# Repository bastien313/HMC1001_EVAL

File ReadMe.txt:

//******************************************************//
//**********	HMC1001 Evaluation board	********//
//**********	    By Bs Electronics           ********//
//**********            04/2019                 ********//
//******************************************************//

Board used to evaluate HMC1001 magnetic sensor.

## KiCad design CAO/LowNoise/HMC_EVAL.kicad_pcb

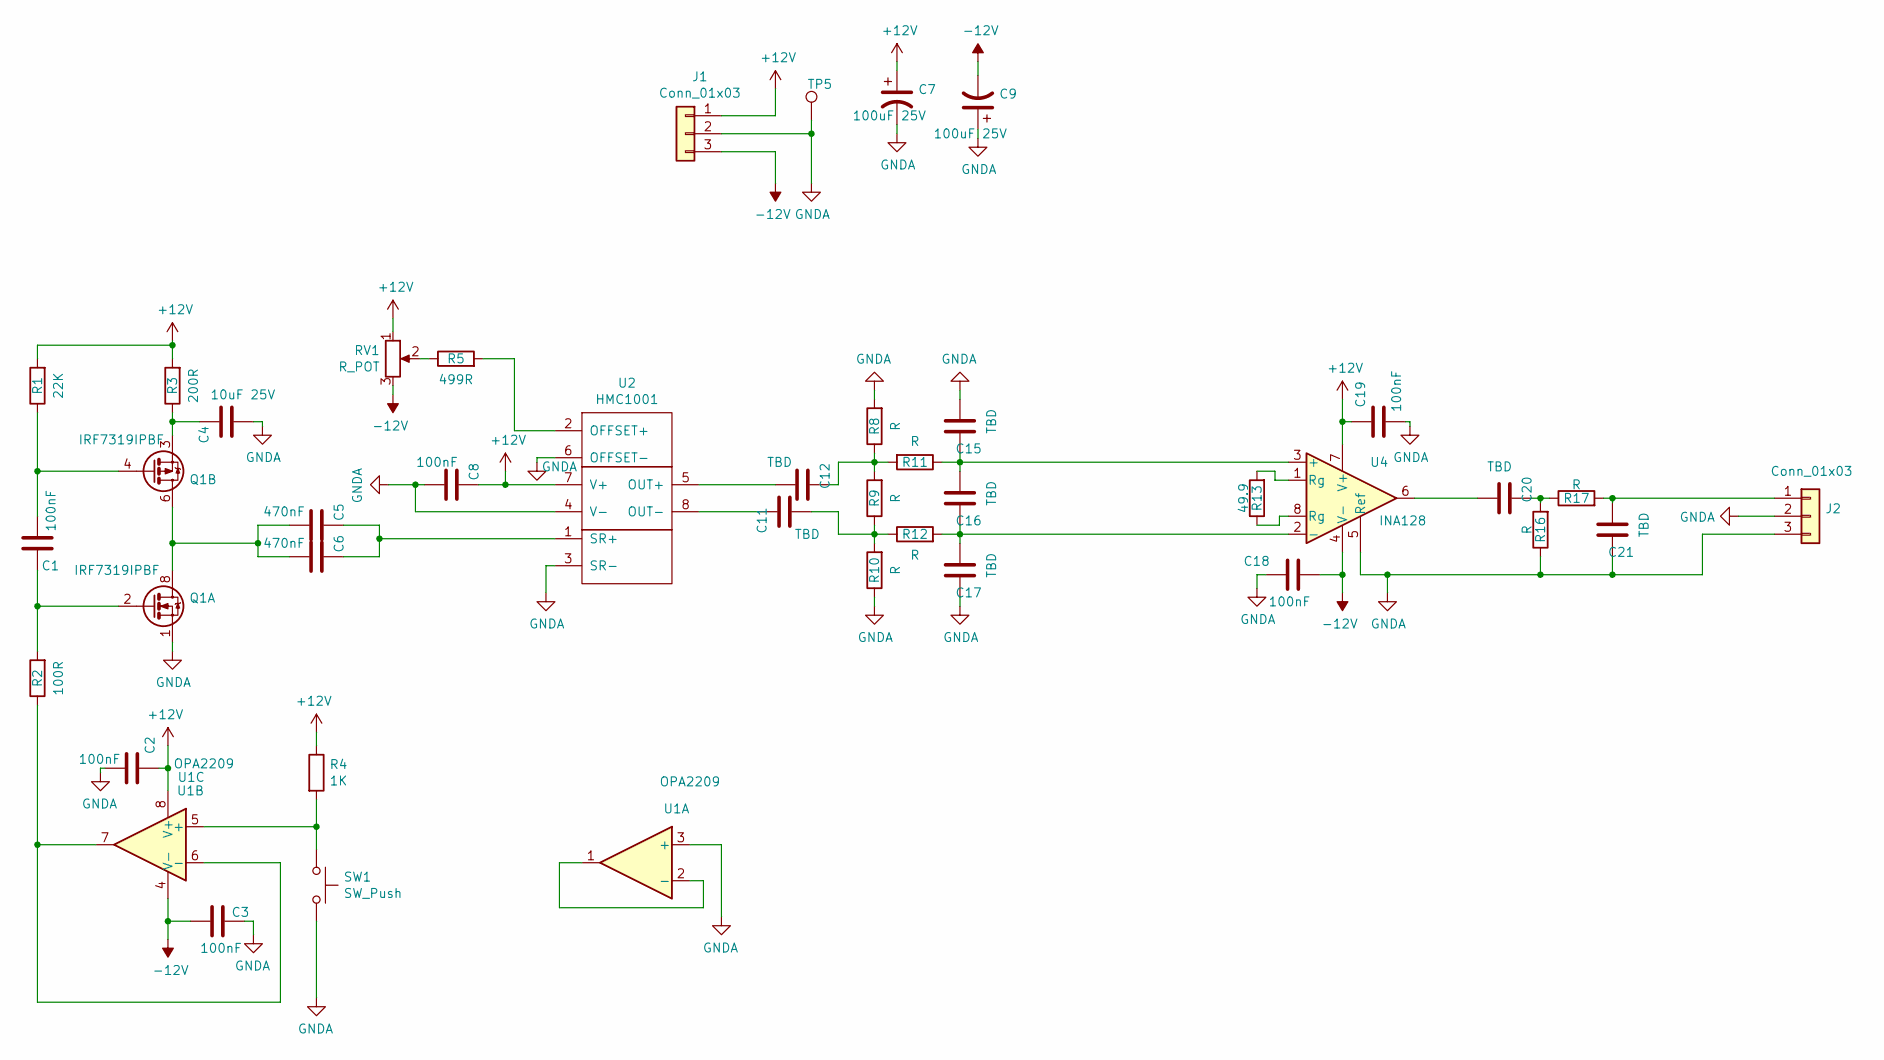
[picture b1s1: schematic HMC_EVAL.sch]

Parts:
C1, C2, C3, C8, C18, C19: 100nF; C_0805_HandSoldering
C4: 10uF 25V; C_1206_HandSoldering
C5, C6: 470nF; C_0805_HandSoldering
C7, C9: 100uF 25V; CP_Radial_D10.0mm_P5.00mm
C11, C12, C15, C16, C17, C20, C21: TBD; C_0805_HandSoldering
J1, J2: Conn_01x03; PhoenixContact_MSTBVA-G_03x5.08mm_Vertical
Q1: IRF7319IPBF; SOIC-8_3.9x4.9mm_Pitch1.27mm
R1: 22K; R_0805_HandSoldering
R2: 100R; R_1206_HandSoldering
R3: 200R; R_1206_HandSoldering
R4: 1K; R_0805_HandSoldering
R5: 499R; R_1206_HandSoldering
R8, R9, R10, R11, R12, R16, R17: R; R_0805_HandSoldering
R13: 49.9; R_0805_HandSoldering
RV1: R_POT; Potentiometer_Trimmer_Bourns_3296W
SW1: SW_Push; FSM2JSMA
TP5: TestPoint; SL-101-X-XX_1x01
U1: OPA2209; SOIC-8_3.9x4.9mm_Pitch1.27mm
U2: HMC1001; HCM1001
U4: INA128; SOIC-8_3.9x4.9mm_Pitch1.27mm

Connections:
+12V: C2.1, C7.1, C8.1, C19.1, J1.1, R1.2, R3.2, R4.1, RV1.1, U1.8 (V+), U2.7 (V+), U4.7 (V+)
-12V: C3.2, C9.2, C18.2, J1.3, RV1.3, U1.4 (V-), U4.4 (V-)
GNDA: C2.2, C3.1, C4.2, C7.2, C8.2, C9.1, C15.2, C17.1, C18.1, C19.2, C21.1, J1.2, J2.2, J2.3, Q1.1 (S), R8.2, R10.1, R16.1, SW1.2, TP5.1, U1.3 (+), U2.3 (SR-), U2.4 (V-), U2.6 (OFFSET-), U4.5 (Ref)
unnamed: C1.1, Q1.2 (G), R2.2
unnamed: C1.2, Q1.4 (G), R1.1
unnamed: C4.1, Q1.3 (1), R3.1
unnamed: C5.1, C6.1, U2.1 (SR+)
unnamed: C5.2, C6.2, Q1.5 (D), Q1.6 (D), Q1.7 (D), Q1.8 (D)
unnamed: C11.1, U2.8 (OUT-)
unnamed: C11.2, R9.1, R10.2, R12.1
unnamed: C12.1, R8.1, R9.2, R11.2
unnamed: C12.2, U2.5 (OUT+)
unnamed: C15.1, C16.2, R11.1, U4.3 (+)
unnamed: C16.1, C17.2, R12.2, U4.2 (-)
unnamed: C20.1, R16.2, R17.1
unnamed 15: C20.2, U4.6; also elsewhere on the board
unnamed: C21.2, J2.1, R17.2
unnamed: R2.1, U1.6 (-), U1.7
unnamed: R4.2, SW1.1, U1.5 (+)
unnamed: R5.1, RV1.2
unnamed: R5.2, U2.2 (OFFSET+)
unnamed: R13.1, U4.8 (Rg)
unnamed: R13.2, U4.1 (Rg)
unnamed: U1.1, U1.2 (-)

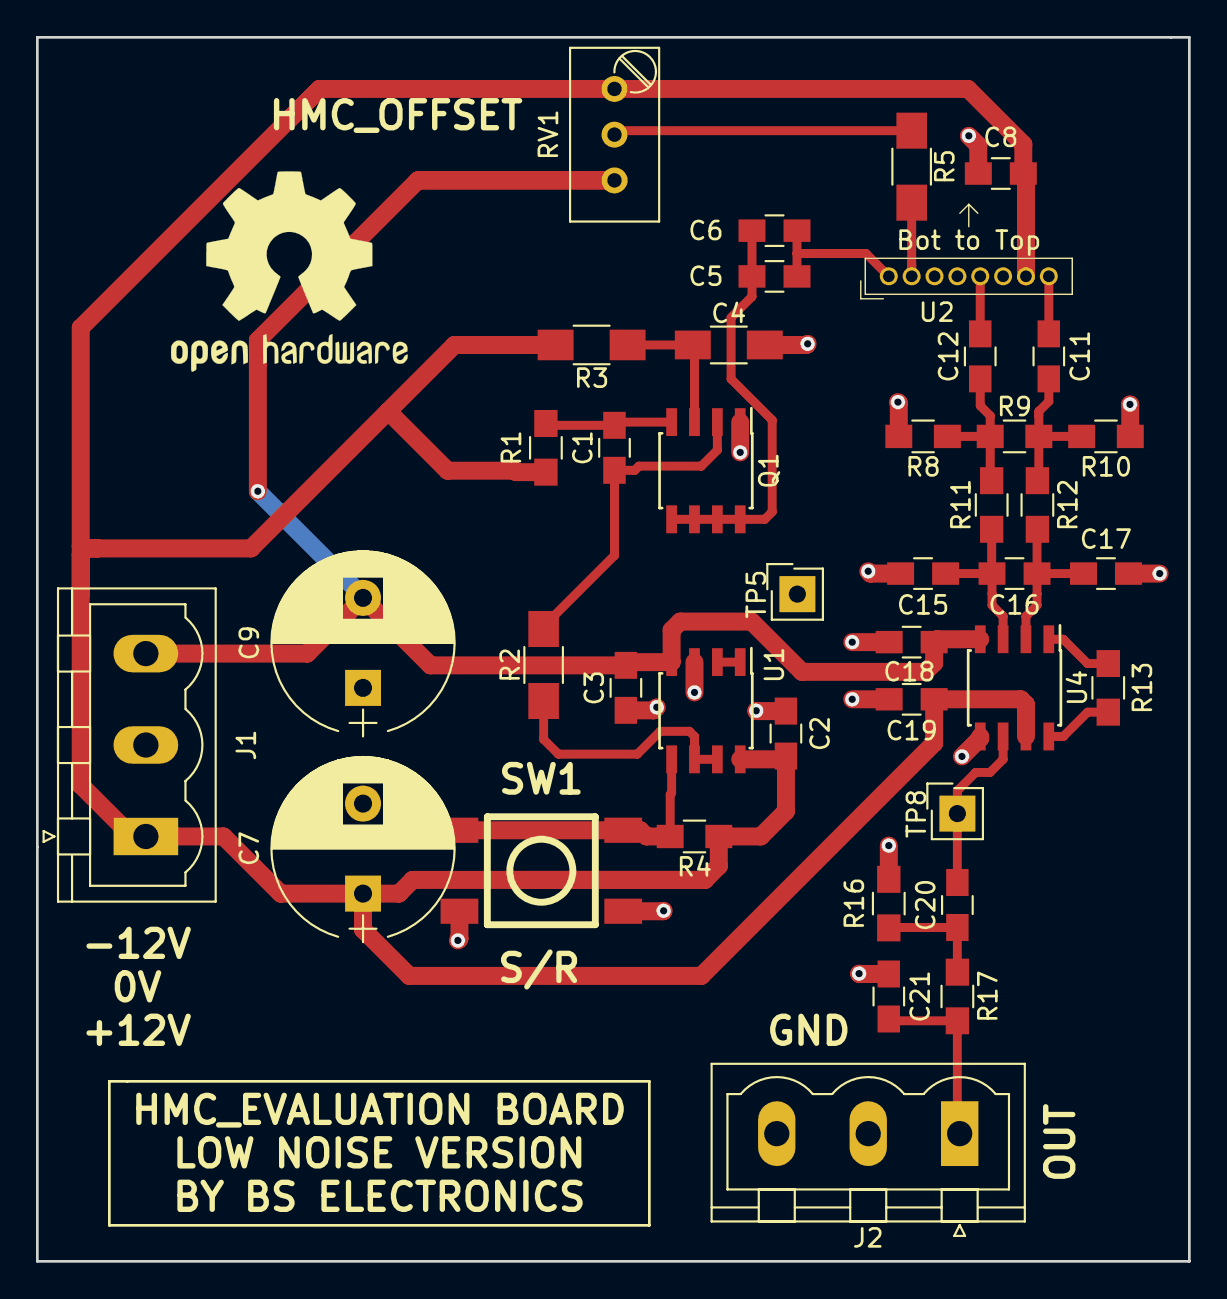
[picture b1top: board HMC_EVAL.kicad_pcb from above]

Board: 2 copper layers, 64.0 x 68.0 mm, 41 parts (0 on the bottom side), 24 nets.

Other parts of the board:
TP8: TestPoint; SL-101-X-XX_1x01

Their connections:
unnamed 15: TP8.1; also elsewhere on the board

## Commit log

2019-04-12 Création of project.
2019-04-12 Add Datasheet
2019-04-13 Creation of schematic
2019-04-13 Finalisation of schemtic. Probably it's necesary to improve design for low noise with less testPoint and Less configuration.
2019-04-13 Add Gnda TestPoint.
2019-04-14 -Suppression of regulator 5V (7805). -Association of components with package.
2019-04-14 Add Library folder for HMC1001.
2019-04-14 Realy add folder library.
2019-04-14 - Standar layout is finish, need to complete fliter resistor and filter capacitor value. - Création of low noise layout.
2019-04-14 - Fix staged files (Git Problem).
2019-04-14 - Low noise version is finish. - Add serigraphi on two design. - Qestion: Copper plane will block low freqency(200hz) magnetic wave??
